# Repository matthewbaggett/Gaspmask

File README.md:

Gaspmask
========

Little driver to live inside a gas mask and drive WS2102 LED rings...

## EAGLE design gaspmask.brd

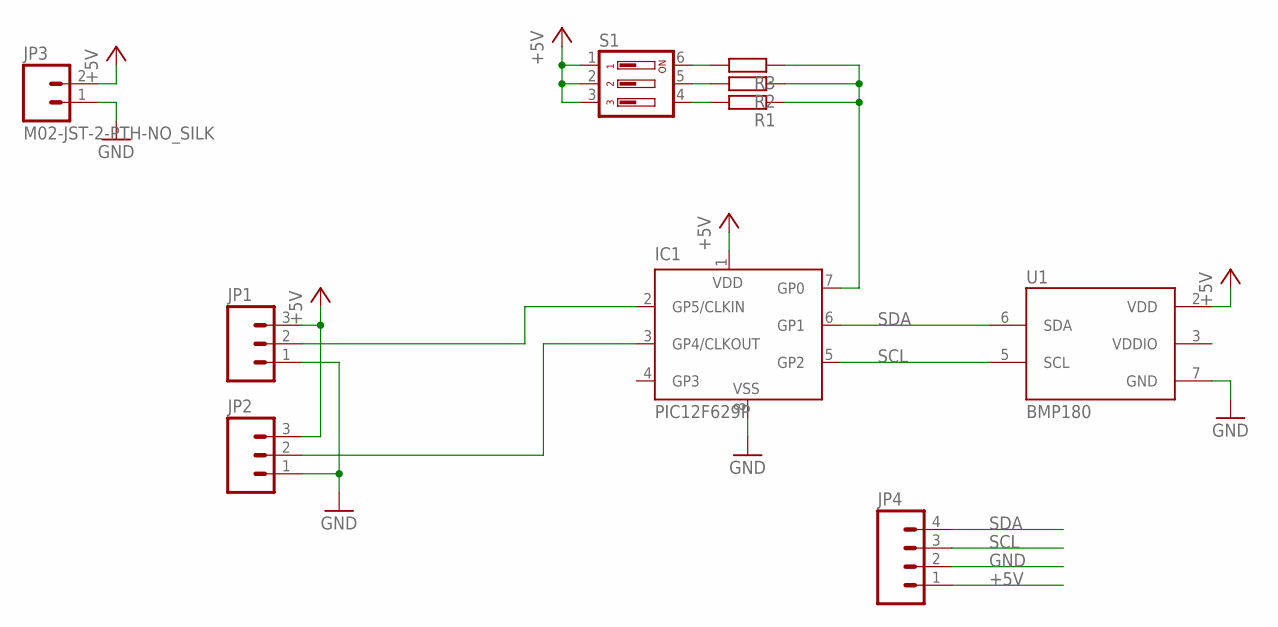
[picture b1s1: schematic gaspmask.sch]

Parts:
IC1: PIC12F629P; DIL8
JP1, JP2: M03JST-PTH; JST-3-PTH
JP3: M02-JST-2-PTH-NO_SILK; JST-2-PTH-NS
JP4: M04LOCK_LONGPADS; 1X04_LOCK_LONGPADS
R1, R2, R3: R-EU_0204/7; 0204/7
S1: DIP03YL
U1: BMP180

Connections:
+5V: IC1.1 (VDD), JP1.3, JP2.3, JP3.2, JP4.1, S1.1, S1.2, S1.3, U1.2 (VDD)
GND: IC1.8 (VSS), JP1.1, JP2.1, JP3.1, JP4.2, U1.7 (GND)
unnamed: IC1.3 (GP4/CLKOUT), JP2.2
unnamed: IC1.2 (GP5/CLKIN), JP1.2
unnamed: R1.2, S1.4
unnamed: R2.2, S1.5
unnamed: R3.2, S1.6
unnamed: IC1.7 (GP0), R1.1, R2.1, R3.1
SCL: IC1.5 (GP2), JP4.3, U1.5 (SCL)
SDA: IC1.6 (GP1), JP4.4, U1.6 (SDA)
VDDIO: U1.3 (VDDIO)

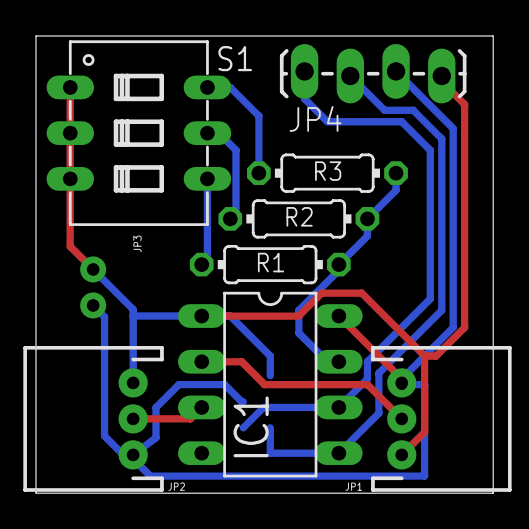
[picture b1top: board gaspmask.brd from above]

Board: 2 copper layers, 25.4 x 25.4 mm, 10 parts (1 on the bottom side), 10 nets.

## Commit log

2014-04-02 Revised to take cheap chinese daughter board.

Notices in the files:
parts and their libraries:
SparkFun-Connectors: Licensing: Creative Commons ShareAlike 4.0 International - https://creativecommons.org/licenses/by-sa/4.0
